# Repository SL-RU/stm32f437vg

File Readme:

Simple devboard for STM32F437VGTx

Screenshot:

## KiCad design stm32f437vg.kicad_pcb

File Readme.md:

Simple devboard for STM32F437VGTx

Screenshot:

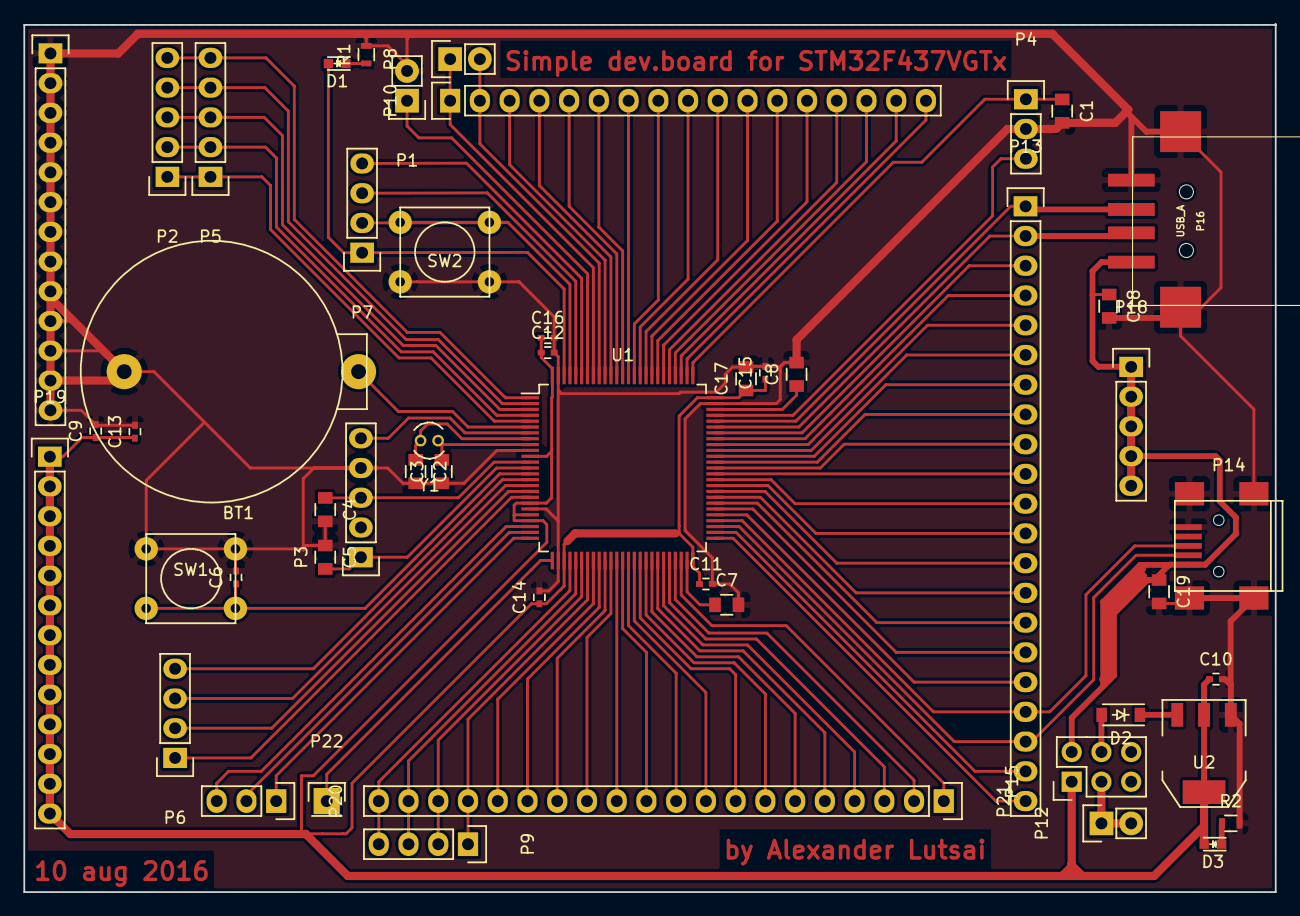
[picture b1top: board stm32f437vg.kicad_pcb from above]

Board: 2 copper layers, 106.9 x 74.1 mm, 51 parts (0 on the bottom side), 95 nets.

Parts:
BT1: Battery; BS-7 CR2032
C1: 100pF; C_0805
C2, C3: 6.5pF; C_0805
C4, C5: 22pF; C_0805
C6, C9, C10, C11, C12, C13, C14, C15, C16: 100nF; C_0402
C7, C8: 2.2uF; C_0805
C17, C18, C19: 4.7uF; C_0805
D1, D3: LED; LED_0603
D2: D_Schottky; SOD-123
P1: CONN_BOOT0; Pin_Header_Straight_1x02
P2, P5, P18: CONN_01X05; Pin_Header_Straight_1x05
P3: CONN_XTAL; Socket_Strip_Straight_1x05
P4: swd; Pin_Header_Straight_1x03
P6, P7, P9: CONN_01X04; Pin_Header_Straight_1x04
P8: CONN_01X02; Pin_Header_Straight_1x02
P10: CONN_01X17; Pin_Header_Straight_1x17
P12: Power 3.3V; Pin_Header_Straight_1x02
P13: CONN_01X21; Pin_Header_Straight_1x21
P14: USB_OTG; USB_Mini-B
P15: CONN_02X03; Pin_Header_Straight_2x03
P16: USB_A; USB-A-SMT-8231-PEG
P17, P19: CONN_01X13; Pin_Header_Straight_1x13
P20: CONN_01X03; Pin_Header_Straight_1x03
P21: CONN_01X20; Pin_Header_Straight_1x20
P22: PA3; Pin_Header_Straight_1x01
R1, R2: 300; R_0603
SW1, SW2: SW_PUSH; SW_PUSH_SMALL
U1: STM32F437VG; LQFP-100_14x14mm_Pitch0.5mm
U2: LM1117-3.3; SOT-223
Y1: Crystal; Crystal_Round_Vertical_3mm

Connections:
+3V3: C9.1, C10.1, C11.1, C12.1, C13.1, C14.1, C15.1, C16.1, C17.1, D3.2, P15.1, P19.1, P19.2, P19.3, P19.4, P19.5, P19.6, P19.7, P19.8, P19.9, P19.10, P19.11, P19.12, P19.13, U1.11, U1.19, U1.21, U1.22, U1.28, U1.50, U1.75, U1.100, U2.2, U2.4
+5V: C18.1, C19.1, P14.1, P15.2, P16.1, P18.1, P18.2, P18.3, P18.4, P18.5
GND: BT1.2, C1.2, C2.2, C3.1, C4.2, C5.1, C6.2, C7.2, C8.2, C9.2, C10.2, C11.2, C12.2, C13.2, C14.2, C15.2, C16.2, C17.2, C18.2, C19.2, P1.2, P3.4, P4.2, P14.5, P14.6, P16.4, P16.5, P17.1, P17.2, P17.3, P17.4, P17.5, P17.6, P17.7, P17.8, P17.9, P17.10, P17.11, P17.12, P17.13, R1.2, R2.2, SW1.1, SW2.1, U1.10, U1.20, U1.27, U1.74, U1.99, U2.1
unnamed: BT1.1, U1.6
unnamed: C1.1, P4.1, U1.76
unnamed: C2.1, U1.8, Y1.2
unnamed: C3.2, U1.9, Y1.1
unnamed: C4.1, P3.3, U1.12
unnamed: C5.2, P3.1, U1.13
unnamed: C6.1, SW1.2, U1.14
unnamed: C7.1, U1.49
unnamed: C8.1, U1.73
unnamed: D1.1, R1.1
unnamed: D1.2, P7.1, U1.98
unnamed: D2.1, U2.3
unnamed: D2.2, P15.4
unnamed: D3.1, R2.1
unnamed: P1.1, U1.94
unnamed: P2.1, P5.1, U1.5
unnamed: P2.2, P5.2, U1.4
unnamed: P2.3, P5.3, U1.3
unnamed: P2.4, P5.4, U1.2
unnamed: P2.5, P5.5, U1.1
unnamed: P3.5, U1.7
unnamed: P4.3, U1.72
unnamed: P6.1, U1.18
unnamed: P6.2, U1.17
unnamed: P6.3, U1.16
unnamed: P6.4, U1.15
unnamed: P7.2, SW2.2, U1.97
unnamed: P7.3, U1.96
unnamed: P7.4, U1.95
unnamed: P8.1, P10.1, U1.93
unnamed: P8.2, P10.2, U1.92
unnamed: P10.3, U1.91
unnamed: P10.4, U1.90
unnamed: P10.5, U1.89
unnamed: P10.6, U1.88
unnamed: P10.7, U1.87
unnamed: P10.8, U1.86
unnamed: P10.9, U1.85
unnamed: P10.10, U1.84
unnamed: P10.11, U1.83
unnamed: P10.12, U1.82
unnamed: P10.13, U1.81
unnamed: P10.14, U1.80
unnamed: P10.15, U1.79
unnamed: P10.16, U1.78
unnamed: P10.17, U1.77
unnamed: P12.1, P12.2, P15.3
unnamed: P13.1, P16.3, U1.71
unnamed: P13.2, P16.2, U1.70
unnamed: P13.3, U1.69
unnamed: P13.4, U1.68
unnamed: P13.5, U1.67
unnamed: P13.6, U1.66
unnamed: P13.7, U1.65
unnamed: P13.8, U1.64
unnamed: P13.9, U1.63
unnamed: P13.10, U1.62
unnamed: P13.11, U1.61
unnamed: P13.12, U1.60
unnamed: P13.13, U1.59
unnamed: P13.14, U1.58
unnamed: P13.15, U1.57
unnamed: P13.16, U1.56
unnamed: P13.17, U1.55
unnamed: P13.18, P14.3, U1.54
unnamed: P13.19, P14.2, U1.53
unnamed: P13.20, U1.52
unnamed: P13.21, U1.51
unnamed: P20.1, U1.25
unnamed: P20.2, U1.24
unnamed: P20.3, U1.23
unnamed: P21.1, U1.48
unnamed: P21.2, U1.47
unnamed: P21.3, U1.46
unnamed: P21.4, U1.45
unnamed: P21.5, U1.44
unnamed: P21.6, U1.43
unnamed: P21.7, U1.42
unnamed: P21.8, U1.41
unnamed: P21.9, U1.40
unnamed: P21.10, U1.39
unnamed: P21.11, U1.38
unnamed: P21.12, U1.37
unnamed: P21.13, U1.36
unnamed: P21.14, U1.35
unnamed: P21.15, U1.34
unnamed: P21.16, U1.33
unnamed: P9.1, P21.17, U1.32
unnamed: P9.2, P21.18, U1.31
unnamed: P9.3, P21.19, U1.30
unnamed: P9.4, P21.20, U1.29
unnamed: P22.1, U1.26

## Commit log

2016-08-09 Component footprints & placed
2016-08-10 pcb done
2016-08-10 pcb fix
2016-08-10 screenshot
2016-08-12 final fix
